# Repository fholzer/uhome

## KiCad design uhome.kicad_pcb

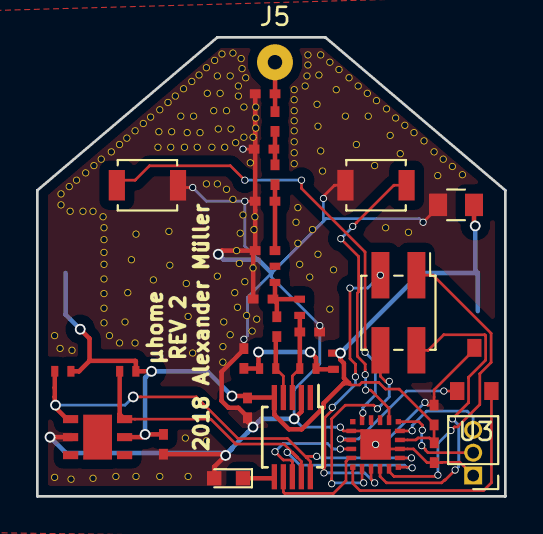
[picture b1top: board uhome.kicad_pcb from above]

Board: 2 copper layers, 26.0 x 25.5 mm, 33 parts (1 on the bottom side), 24 nets.

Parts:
BT1: Battery_Cell; BAT-HLD-001
C1, C4: 1µ; C_0402_NoSilk
C2, C3: 0.1µ; C_0402_NoSilk
C5, C7: 4.5pF; C_0402_NoSilk
C6: 15pF; C_0402_NoSilk
C8: 20µ; C_0805
C9: CM6 (6.8pF); C_0402_NoSilk
C10: CM5 (6.8pF); C_0402_NoSilk
C11: CM1 (4.3pF); C_0402_NoSilk
C12: CM2 (1.8 pF); C_0402_NoSilk
C13: CM3 (2.7pF); C_0402_NoSilk
D1: LED; LED_0603
J1: C2; Pin_Header_Straight_1x03_Pitch1.27mm
J2, J4: Conn_01x02; SW_SPST_B3U-1000P
J3: Conn_01x04; Pin_Header_Straight_2x02_Pitch2.00mm_SMD
J5: ANT; SolderWirePad_single_0-8mmDrill
L1, L2: 30nH; C_0402_NoSilk
L3: LM5 (18nH); R_0402_NoSilk
L4: LM3 (56 nH); R_0402_NoSilk
L5: LM2 (16 nH); R_0402_NoSilk
L6: LM4 (16 nH); R_0402_NoSilk
L7: LM1 (220 nH); R_0402_NoSilk
R1, R2: 10k; R_0402_NoSilk
U1: Si7006
U2: EFM8SB10; 20-UFQFN
U3: AH1806; SC59
U4: Si4012; MSOP-10_3x3mm_Pitch0.5mm

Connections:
+BATT: BT1.1, C1.1, C2.1, C3.1, C4.2, C8.2, L7.1, R1.1, R2.1, U1.5, U2.4, U4.5
ANT_M: C11.2, L4.1, L5.1, U4.3
ANT_P: C12.2, L6.2, U4.4
GND: BT1.2, C1.2, C2.2, C3.2, C4.1, C5.2, C6.2, C7.2, C8.1, C9.2, C10.2, C11.1, C13.2, D1.2, J1.1, J2.2, J4.1, U1.2, U2.3, U2.12, U2.21, U3.2, U4.2
I2C_SCL: R2.2, U1.6, U2.1, U4.9
I2C_SDA: R1.2, U1.1, U2.2, U4.10
unnamed: C5.1, J5.1, L1.2
unnamed: C6.1, L1.1, L2.2
unnamed: C7.1, C9.1, L2.1, L3.2
unnamed: C10.1, C12.1, L3.1, L4.2
unnamed: C13.1, L5.2, L6.1, L7.2
unnamed: D1.1, U4.6
unnamed: J1.2, U2.6
unnamed: J1.3, U2.5
unnamed: J2.1, U2.7
unnamed: J3.1, U2.20
unnamed: J3.2, U2.19
unnamed: J3.3, U2.18
unnamed: J3.4, U2.17
unnamed: J4.2, U2.10
unnamed: U2.13, U3.1
unnamed: U2.16, U3.3
TRX_IRQ: U2.15, U4.7
TRX_SDN: U2.14, U4.8

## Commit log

2018-03-13 Updated gitignore
2018-03-13 Added schematic and board
2018-04-02 Revision 2
2018-04-02 Cleanup
2018-04-02 Added picture of pcb
2018-04-02 Added pic of rev1
2018-04-09 Added CRC calculation
2018-04-10 Added rtl_433
2018-04-13 Refactoring:
    * check crc or magic number before processing payload
    * extract crc calculation function
    * verify temperature and humidity sensor readings, set to "-1.0" on failure
    * return number of successfully read messages
2018-04-13 Fix defaults
2018-04-13 Fix overflow when evaluating sensor data
